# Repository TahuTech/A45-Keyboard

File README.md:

# A45-Keyboard

The Cheap Layout of TMO50

- Use Pro Micro
- Adjust On Bottom Row
- Hotswap

.jpg)
.jpg)
.jpg)

for scuff typing test
https://www.youtube.com/watch?v=yLzhY9SzVdQ

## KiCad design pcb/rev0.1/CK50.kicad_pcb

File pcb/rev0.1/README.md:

- fix issue on schematic
- upgrade hotswap footprint
- fix routing on diode
- better routing
- add led for top macro cluster
- add reset button

how next ?

- maybe change position for pro micro to macro cluster
- reduce size pcb

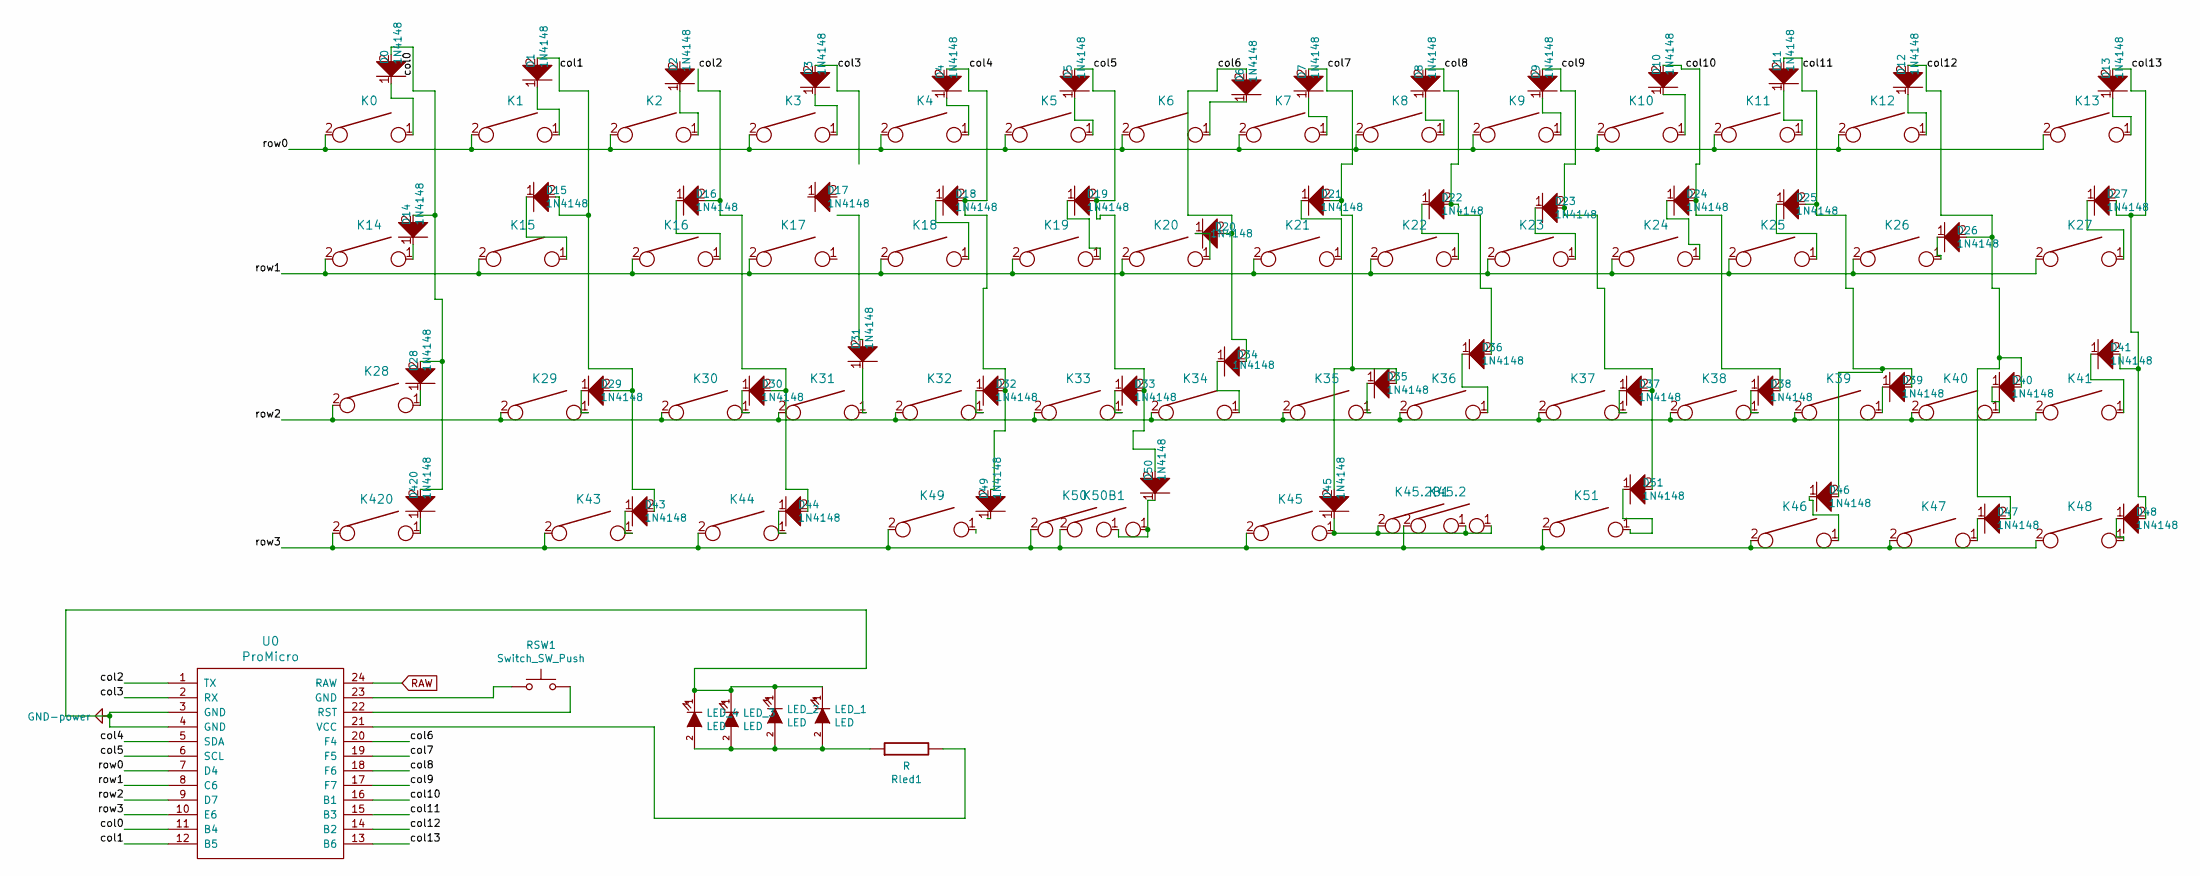
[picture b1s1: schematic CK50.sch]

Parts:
D0, D1, D2, D3, D4, D5, D6, D7, D8, D9, D10, D11, D12, D13, D14, D15, D16, D17, D18, D19, D20, D21, D22, D23, D24, D25, D26, D27, D28, D29, D30, D31, D32, D33, D34, D35, D36, D37, D38, D39, D40, D41, D43, D44, D45, D46, D47, D48, D49, D50, D51, D420: 1N4148; Diode-dual
K0, K1, K2, K3, K4, K5, K6, K7, K8, K9, K10, K11, K12, K13, K14, K16, K17, K18, K19, K20, K21, K22, K23, K24, K25, K27, K28, K30, K31, K32, K33, K34, K35, K36, K37, K38, K39, K41, K43, K47, K48, K420: KEYSW; MX_PCB_100H
K15, K40, K44, K46: KEYSW; MX_PCB_125H
K26, K29: KEYSW; MX_PCB_175H
K45, K45.2, K49, K50, K51: KEYSW; MX_PCB_700H
K45.2B1, K50B1: KEYSW
LED_1, LED_2, LED_3, LED_4: LED
RSW1: Switch_SW_Push
Rled1: R
U0: ProMicro; ArduinoProMicro

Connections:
/col0: D0.2, D14.2, D28.2, D420.2, U0.11 (B4)
/col1: D1.2, D15.2, D29.2, D43.2, U0.12 (B5)
/col2: D16.2, D30.2, D44.2, U0.1 (TX)
/col3: D3.2, U0.2 (RX)
/col4: D4.2, D18.2, D32.2, D49.2, U0.5 (SDA)
/col5: D5.2, D19.2, D33.2, D50.2, U0.6 (SCL)
/col6: D6.2, D20.2, D34.2, U0.20 (F4)
/col7: D7.2, D21.2, D35.2, D45.2, U0.19 (F5)
/col8: D8.2, D22.2, D36.2, U0.18 (F6)
/col9: D9.2, D23.2, D37.2, D51.2, U0.17 (F7)
/col10: D10.2, D24.2, D38.2, U0.16 (B1)
/col11: D11.2, D25.2, D39.2, D46.2, U0.15 (B3)
/col12: D12.2, D26.2, D40.2, D47.2, U0.14 (B2)
/col13: D13.2, D27.2, D41.2, D48.2, U0.13 (B6)
/row0: K0.2, K1.2, K2.2, K3.2, K4.2, K5.2, K6.2, K7.2, K8.2, K9.2, K10.2, K11.2, K12.2, K13.2, U0.7 (D4)
/row1: K14.2, K15.2, K16.2, K17.2, K18.2, K19.2, K20.2, K21.2, K22.2, K23.2, K24.2, K25.2, K26.2, K27.2, U0.8 (C6)
/row2: K28.2, K29.2, K30.2, K31.2, K32.2, K33.2, K34.2, K35.2, K36.2, K37.2, K38.2, K39.2, K40.2, K41.2, U0.9 (D7)
/row3: K43.2, K44.2, K45.2, K45.2.2, K46.2, K47.2, K48.2, K49.2, K50.2, K50B1.2, K51.2, K420.2, U0.10 (E6); also elsewhere on the board
GND: LED_1.1 (K), LED_2.1 (K), LED_3.1 (K), LED_4.1 (K), U0.3 (GND), U0.4 (GND)
unnamed: D0.1, K0.1
unnamed: D1.1, K1.1
unnamed: D2.1, K2.1
unnamed: D3.1, K3.1
unnamed: D4.1, K4.1
unnamed: D5.1, K5.1
unnamed: D6.1, K6.1
unnamed: D7.1, K7.1
unnamed: D8.1, K8.1
unnamed: D9.1, K9.1
unnamed: D10.1, K10.1
unnamed: D11.1, K11.1
unnamed: D12.1, K12.1
unnamed: D13.1, K13.1
unnamed: D14.1, K14.1
unnamed: D15.1, K15.1
unnamed: D16.1, K16.1
unnamed: D18.1, K18.1
unnamed: D19.1, K19.1
unnamed: D20.1, K20.1
unnamed: D21.1, K21.1
unnamed: D22.1, K22.1
unnamed: D23.1, K23.1
unnamed: D24.1, K24.1
unnamed: D25.1, K25.1
unnamed: D26.1, K26.1
unnamed: D27.1, K27.1
unnamed: D28.1, K28.1
unnamed: D29.1, K29.1
unnamed: D30.1, K30.1
unnamed: D31.1, K31.1
unnamed: D32.1, K32.1
unnamed: D33.1, K33.1
unnamed: D34.1, K34.1
unnamed: D35.1, K35.1
unnamed: D36.1, K36.1
unnamed: D37.1, K37.1
unnamed: D38.1, K38.1
unnamed: D39.1, K39.1
unnamed: D40.1, K40.1
unnamed: D41.1, K41.1
unnamed: D43.1, K43.1
unnamed: D44.1, K44.1
unnamed 66: D45.1, K45.1, K45.2.1, K45.2B1.1, K45.2B1.2; also elsewhere on the board
unnamed: D46.1, K46.1
unnamed: D47.1, K47.1
unnamed: D48.1, K48.1
unnamed 71: D50.1, K50.1, K50B1.1; also elsewhere on the board
unnamed: D51.1, K51.1
unnamed: D420.1, K420.1
unnamed: LED_1.2 (A), LED_2.2 (A), LED_3.2 (A), LED_4.2 (A), Rled1.1
unnamed: RSW1.1, U0.23 (GND)
unnamed: RSW1.2, U0.22 (RST)
unnamed: Rled1.2, U0.21 (VCC)
RAW: U0.24 (RAW)

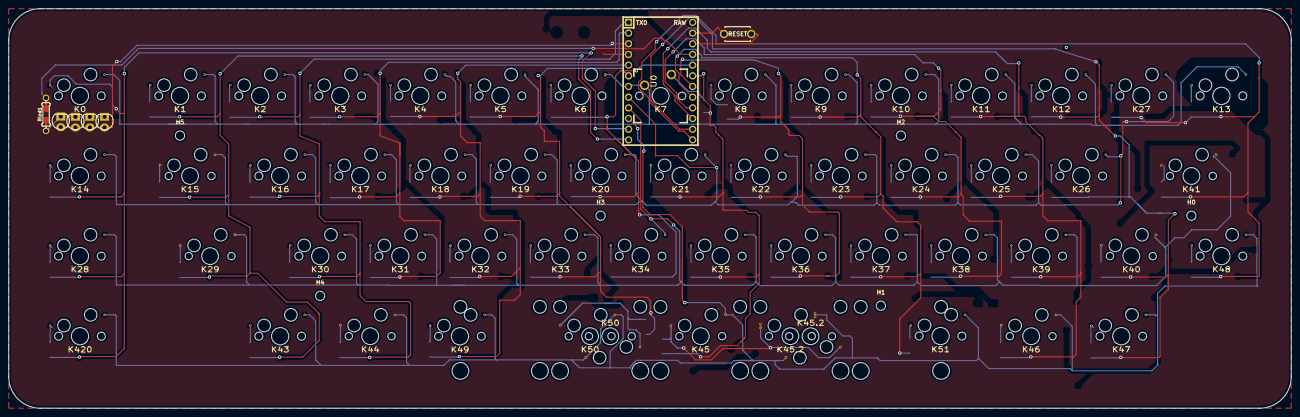
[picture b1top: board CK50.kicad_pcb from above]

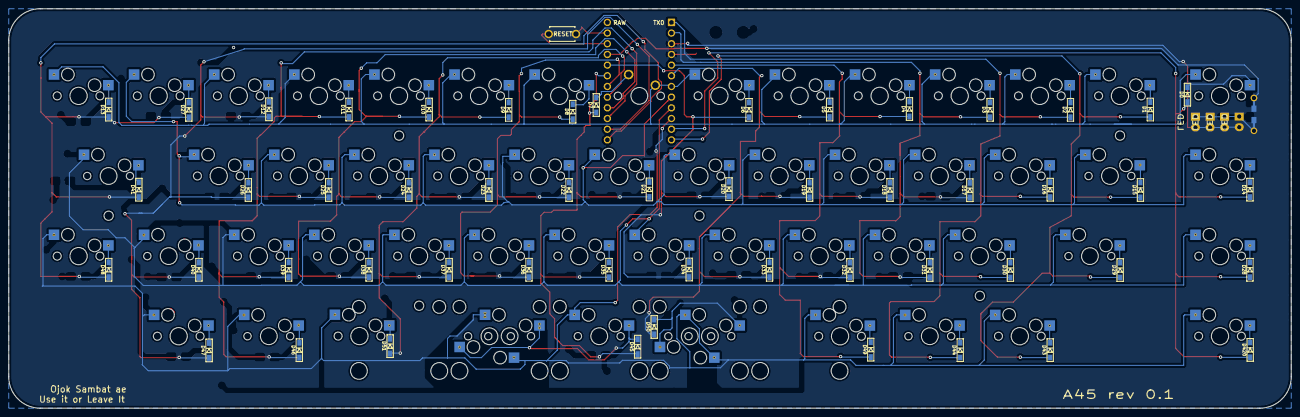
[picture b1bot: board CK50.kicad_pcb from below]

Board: 2 copper layers, 305.0 x 95.0 mm, 120 parts (52 on the bottom side), 73 nets.

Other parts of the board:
H0, H1, H2, H3, H4, H5: MountingHole_2.2mm_M2
K45.2#2: KEYSW; MXOnly-2.75U-Hotswap-MOD
K50#2: KEYSW; MXOnly-2.75U-Hotswap-ReversedStabilizers-MOD

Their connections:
/row3: K45.2#2.2, K50#2.2; also elsewhere on the board
unnamed 66: K45.2#2.1; also elsewhere on the board
unnamed 71: K50#2.1; also elsewhere on the board

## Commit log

2022-01-02 add_proto_gerber
2022-01-02 add rev0.1
2022-01-02 add prototype
2022-01-02 version info
2022-01-02 prototype notes
2022-01-02 add notes
2022-12-01 add pcb details
2022-12-01 add case & img
2022-12-01 add IMG
